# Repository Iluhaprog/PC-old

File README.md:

# Computer from scratch 

## Control unit

Операции
1. Сложение
2. Вычитание
3. Сдвиг влево
4. Сдвиг вправо
5. Записать значение в регистр A
6. Записать значение в регистр B
7. Условный переход при A > B
8. Условный переход при A < B
9. Условный переход при A = B
10. Завершить программу

> ### Условные обозначения
> 
> **RW**: read - "0", write - "1"
> 
> **EN**: enable - "1", disable - "0"
> 
> **HS**: hide - "1", show- "0"

> ### Устройства:
> - СК - Счетчик команд
> - РКК - Регистр кода команды
> - РА - Регистр А
> - РВ - Регистр В
> - РПА - Регистр пользовательского адреса
> - РР - Регистр результата
> - АЛУ - Арифметико-логичекое устройство
> - РФ - Регистр флагов

<h2>Формат команды</h2>
<div style="padding: 20px 10px 10px 20px; border-left: 2px solid grey; margin-bottom: 20px">

<span style="border: 3px solid orange">**код операции**</span>
<span style="border: 3px solid pink">адрес</span>

</div>

### 1. Операция сложения 

Код операции - **0001**

Адрес - номер места в ОЗУ, куда необходимо записать результат

Действия для выполнения:

1. Выключаем счетчик команд
2. Включаем чтение из ОЗУ **[R]** `0`
3. Включаем выводы ОЗУ **[EN]** `1` на чтение
4. Включаем запись в регистр пользовательских адресов (РПА) **[R]** `1`
5. Включаем выводы РПА **[EN]** для записи `1`
6. Выключаем выводы РПА **[EN]**  для записи `0`
7. Включаем запись в регистр кода команды (РКК) **[W]** `1`
8. Включаем выводы РКК **[EN]** для записи `1`
9. Выключаем выводы РКК **[EN]**  для записи `0`
10. Включаем чтение из РКК **[R]** `1`
11. Включаем выводы РКК **[EN]** для чтения `0`
12. Включаем выводы **Mode** `1`
13. Выключаем выводы ОЗУ **[EN]** `0` на чтение
14. Включаем выводы АЛУ **[EN]** для чтения
15. Включаем на запись регистр результата (РР) **[W]** `1`
16. Включаем выводы РР **[EN]** `1` для записи
17. Выключаем выводы РР **[EN]** `0` для записи
18. Выключаем выводы AЛУ **[EN]** `0` для чтения
19. Включаем чтение РР **[R]** `0`
20. Включаем выводы РР **[EN]** `1` для чтения
21. Выключаем вывод адреса из счетчика команд **[HS]** `1`
22. Включаем чтение РПА **[R]** `0`
23. Включаем выводы РПА **[EN]** `1` для чтения
24. Включаем ОЗУ на запись **[W]** `1`
25. Включаем выводы ОЗУ  **[EN]** `1` для записи
26. Выключаем выводы ОЗУ  **[EN]** `0` для записи
27. Выключаем выводы РПА **[EN]** `0` для чтения
28. Включаем вывод адреса из счетчика команд **[HS]** `0`
29. Выключаем выводы РР **[EN]** `0` для чтения
30. Включаем счетчик команд

Выводы :
1. EN СК
2. HS CK
3. EN ОЗУ
4. RW ОЗУ
5. EN РКК
6. RW РКК
7. EN PA
8. RW PA
9. EN PB
10. RW PB
11. EN PP
12. RW PP
13. EN РПА
14. RW РПА
15. АЛУ 1-бит (для выбора варианта работы АЛУ)
16. АЛУ 2-бит (для выбора варианта работы АЛУ)
17. EN АЛУ (чтение с выхода)
18. EN РФ
19. RW РФ

| Такт | Состояния на выходе   | Действия                   |
|------|-----------------------|----------------------------|
| 1    | 0010110000001100000   | 1,2,3,4,5,6,7,8            |
| 2    | 0000101010110000100   | 9,10,11,12,13,14,15,16     |
| 3    | 0111000000101000000   | 16,17,18,19,20,21,22,23,24 |
| 4    | 1000000000000000000   | 24,25,26,27,28,28,30       |

### 2. Операция вычитания 

Код операции - **0010**

Адрес - номер места в ОЗУ, куда необходимо записать результат

Действия для выполнения:

1. Выключаем счетчик команд
2. Включаем чтение из ОЗУ **[R]** `0`
3. Включаем выводы ОЗУ **[EN]** `1` на чтение
4. Включаем запись в регистр пользовательских адресов (РПА) **[R]** `1`
5. Включаем выводы РПА **[EN]** для записи `1`
6. Выключаем выводы РПА **[EN]**  для записи `0`
7. Включаем запись в регистр кода команды (РКК) **[W]** `1`
8. Включаем выводы РКК **[EN]** для записи `1`
9. Выключаем выводы РКК **[EN]**  для записи `0`
10. Включаем чтение из РКК **[R]** `1`
11. Включаем выводы РКК **[EN]** для чтения `0`
12. Включаем выводы **Mode** `10`
13. Выключаем выводы ОЗУ **[EN]** `0` на чтение
14. Включаем выводы АЛУ **[EN]** для чтения
15. Включаем на запись регистр результата (РР) **[W]** `1`
16. Включаем выводы РР **[EN]** `1` для записи
17. Выключаем выводы РР **[EN]** `0` для записи
18. Выключаем выводы AЛУ **[EN]** `0` для чтения
19. Включаем чтение РР **[R]** `0`
20. Включаем выводы РР **[EN]** `1` для чтения
21. Выключаем вывод адреса из счетчика команд **[HS]** `1`
22. Включаем чтение РПА **[R]** `0`
23. Включаем выводы РПА **[EN]** `1` для чтения
24. Включаем ОЗУ на запись **[W]** `1`
25. Включаем выводы ОЗУ  **[EN]** `1` для записи
26. Выключаем выводы ОЗУ  **[EN]** `0` для записи
27. Выключаем выводы РПА **[EN]** `0` для чтения
28. Включаем вывод адреса из счетчика команд **[HS]** `0`
29. Выключаем выводы РР **[EN]** `0` для чтения
30. Включаем счетчик команд

Выводы :
1. EN СК
2. HS CK
3. EN ОЗУ
4. RW ОЗУ
5. EN РКК
6. RW РКК
7. EN PA
8. RW PA
9. EN PB
10. RW PB
11. EN PP
12. RW PP
13. EN РПА
14. RW РПА
15. АЛУ 1-бит (для выбора варианта работы АЛУ)
16. АЛУ 2-бит (для выбора варианта работы АЛУ)
17. EN АЛУ (чтение с выхода)
18. EN РФ
19. RW РФ

| Такт | Состояния на выходе   | Действия                   |
|------|-----------------------|----------------------------|
| 1    | 0010110000001100000   | 1,2,3,4,5,6,7,8            |
| 2    | 0000101010110010100   | 9,10,11,12,13,14,15,16     |
| 3    | 0111000000101000000   | 16,17,18,19,20,21,22,23,24 |
| 4    | 1000000000000000000   | 24,25,26,27,28,28,30       |

### 3. Операция сдвига влево 

Код операции - **0011**

Адрес - номер места в ОЗУ, куда необходимо записать результат

Действия для выполнения:

1. Выключаем счетчик команд
2. Включаем чтение из ОЗУ **[R]** `0`
3. Включаем выводы ОЗУ **[EN]** `1` на чтение
4. Включаем запись в регистр пользовательских адресов (РПА) **[R]** `1`
5. Включаем выводы РПА **[EN]** для записи `1`
6. Выключаем выводы РПА **[EN]**  для записи `0`
7. Включаем запись в регистр кода команды (РКК) **[W]** `1`
8. Включаем выводы РКК **[EN]** для записи `1`
9. Выключаем выводы РКК **[EN]**  для записи `0`
10. Включаем чтение из РКК **[R]** `1`
11. Включаем выводы РКК **[EN]** для чтения `0`
12. Включаем выводы **Mode** `11`
13. Выключаем выводы ОЗУ **[EN]** `0` на чтение
14. Включаем выводы АЛУ **[EN]** для чтения
15. Включаем на запись регистр результата (РР) **[W]** `1`
16. Включаем выводы РР **[EN]** `1` для записи
17. Выключаем выводы РР **[EN]** `0` для записи
18. Выключаем выводы AЛУ **[EN]** `0` для чтения
19. Включаем чтение РР **[R]** `0`
20. Включаем выводы РР **[EN]** `1` для чтения
21. Выключаем вывод адреса из счетчика команд **[HS]** `1`
22. Включаем чтение РПА **[R]** `0`
23. Включаем выводы РПА **[EN]** `1` для чтения
24. Включаем ОЗУ на запись **[W]** `1`
25. Включаем выводы ОЗУ  **[EN]** `1` для записи
26. Выключаем выводы ОЗУ  **[EN]** `0` для записи
27. Выключаем выводы РПА **[EN]** `0` для чтения
28. Включаем вывод адреса из счетчика команд **[HS]** `0`
29. Выключаем выводы РР **[EN]** `0` для чтения
30. Включаем счетчик команд

Выводы :
1. EN СК
2. HS CK
3. EN ОЗУ
4. RW ОЗУ
5. EN РКК
6. RW РКК
7. EN PA
8. RW PA
9. EN PB
10. RW PB
11. EN PP
12. RW PP
13. EN РПА
14. RW РПА
15. АЛУ 1-бит (для выбора варианта работы АЛУ)
16. АЛУ 2-бит (для выбора варианта работы АЛУ)
17. EN АЛУ (чтение с выхода)
18. EN РФ
19. RW РФ

| Такт | Состояния на выходе   | Действия                   |
|------|-----------------------|----------------------------|
| 1    | 0010110000001100000   | 1,2,3,4,5,6,7,8            |
| 2    | 0000101010110011100   | 9,10,11,12,13,14,15,16     |
| 3    | 0111000000101000000   | 16,17,18,19,20,21,22,23,24 |
| 4    | 1000000000000000000   | 24,25,26,27,28,28,30       |

### 3. Операция сдвига вправо 

Код операции - **0100**

Адрес - номер места в ОЗУ, куда необходимо записать результат

Действия для выполнения:

1. Выключаем счетчик команд
2. Включаем чтение из ОЗУ **[R]** `0`
3. Включаем выводы ОЗУ **[EN]** `1` на чтение
4. Включаем запись в регистр пользовательских адресов (РПА) **[R]** `1`
5. Включаем выводы РПА **[EN]** для записи `1`
6. Выключаем выводы РПА **[EN]**  для записи `0`
7. Включаем запись в регистр кода команды (РКК) **[W]** `1`
8. Включаем выводы РКК **[EN]** для записи `1`
9. Выключаем выводы РКК **[EN]**  для записи `0`
10. Включаем чтение из РКК **[R]** `1`
11. Включаем выводы РКК **[EN]** для чтения `0`
12. Включаем выводы **Mode** `11`
13. Выключаем выводы ОЗУ **[EN]** `0` на чтение
14. Включаем выводы АЛУ **[EN]** для чтения
15. Включаем на запись регистр результата (РР) **[W]** `1`
16. Включаем выводы РР **[EN]** `1` для записи
17. Выключаем выводы РР **[EN]** `0` для записи
18. Выключаем выводы AЛУ **[EN]** `0` для чтения
19. Включаем чтение РР **[R]** `0`
20. Включаем выводы РР **[EN]** `1` для чтения
21. Выключаем вывод адреса из счетчика команд **[HS]** `1`
22. Включаем чтение РПА **[R]** `0`
23. Включаем выводы РПА **[EN]** `1` для чтения
24. Включаем ОЗУ на запись **[W]** `1`
25. Включаем выводы ОЗУ  **[EN]** `1` для записи
26. Выключаем выводы ОЗУ  **[EN]** `0` для записи
27. Выключаем выводы РПА **[EN]** `0` для чтения
28. Включаем вывод адреса из счетчика команд **[HS]** `0`
29. Выключаем выводы РР **[EN]** `0` для чтения
30. Включаем счетчик команд

Выводы :
1. EN СК
2. HS CK
3. EN ОЗУ
4. RW ОЗУ
5. EN РКК
6. RW РКК
7. EN PA
8. RW PA
9. EN PB
10. RW PB
11. EN PP
12. RW PP
13. EN РПА
14. RW РПА
15. АЛУ 1-бит (для выбора варианта работы АЛУ)
16. АЛУ 2-бит (для выбора варианта работы АЛУ)
17. EN АЛУ (чтение с выхода)
18. EN РФ
19. RW РФ

| Такт | Состояния на выходе   | Действия                   |
|------|-----------------------|----------------------------|
| 1    | 0010110000001100000   | 1,2,3,4,5,6,7,8            |
| 2    | 0000101010110001100   | 9,10,11,12,13,14,15,16     |
| 3    | 0111000000101000000   | 16,17,18,19,20,21,22,23,24 |
| 4    | 1000000000000000000   | 24,25,26,27,28,28,30       |

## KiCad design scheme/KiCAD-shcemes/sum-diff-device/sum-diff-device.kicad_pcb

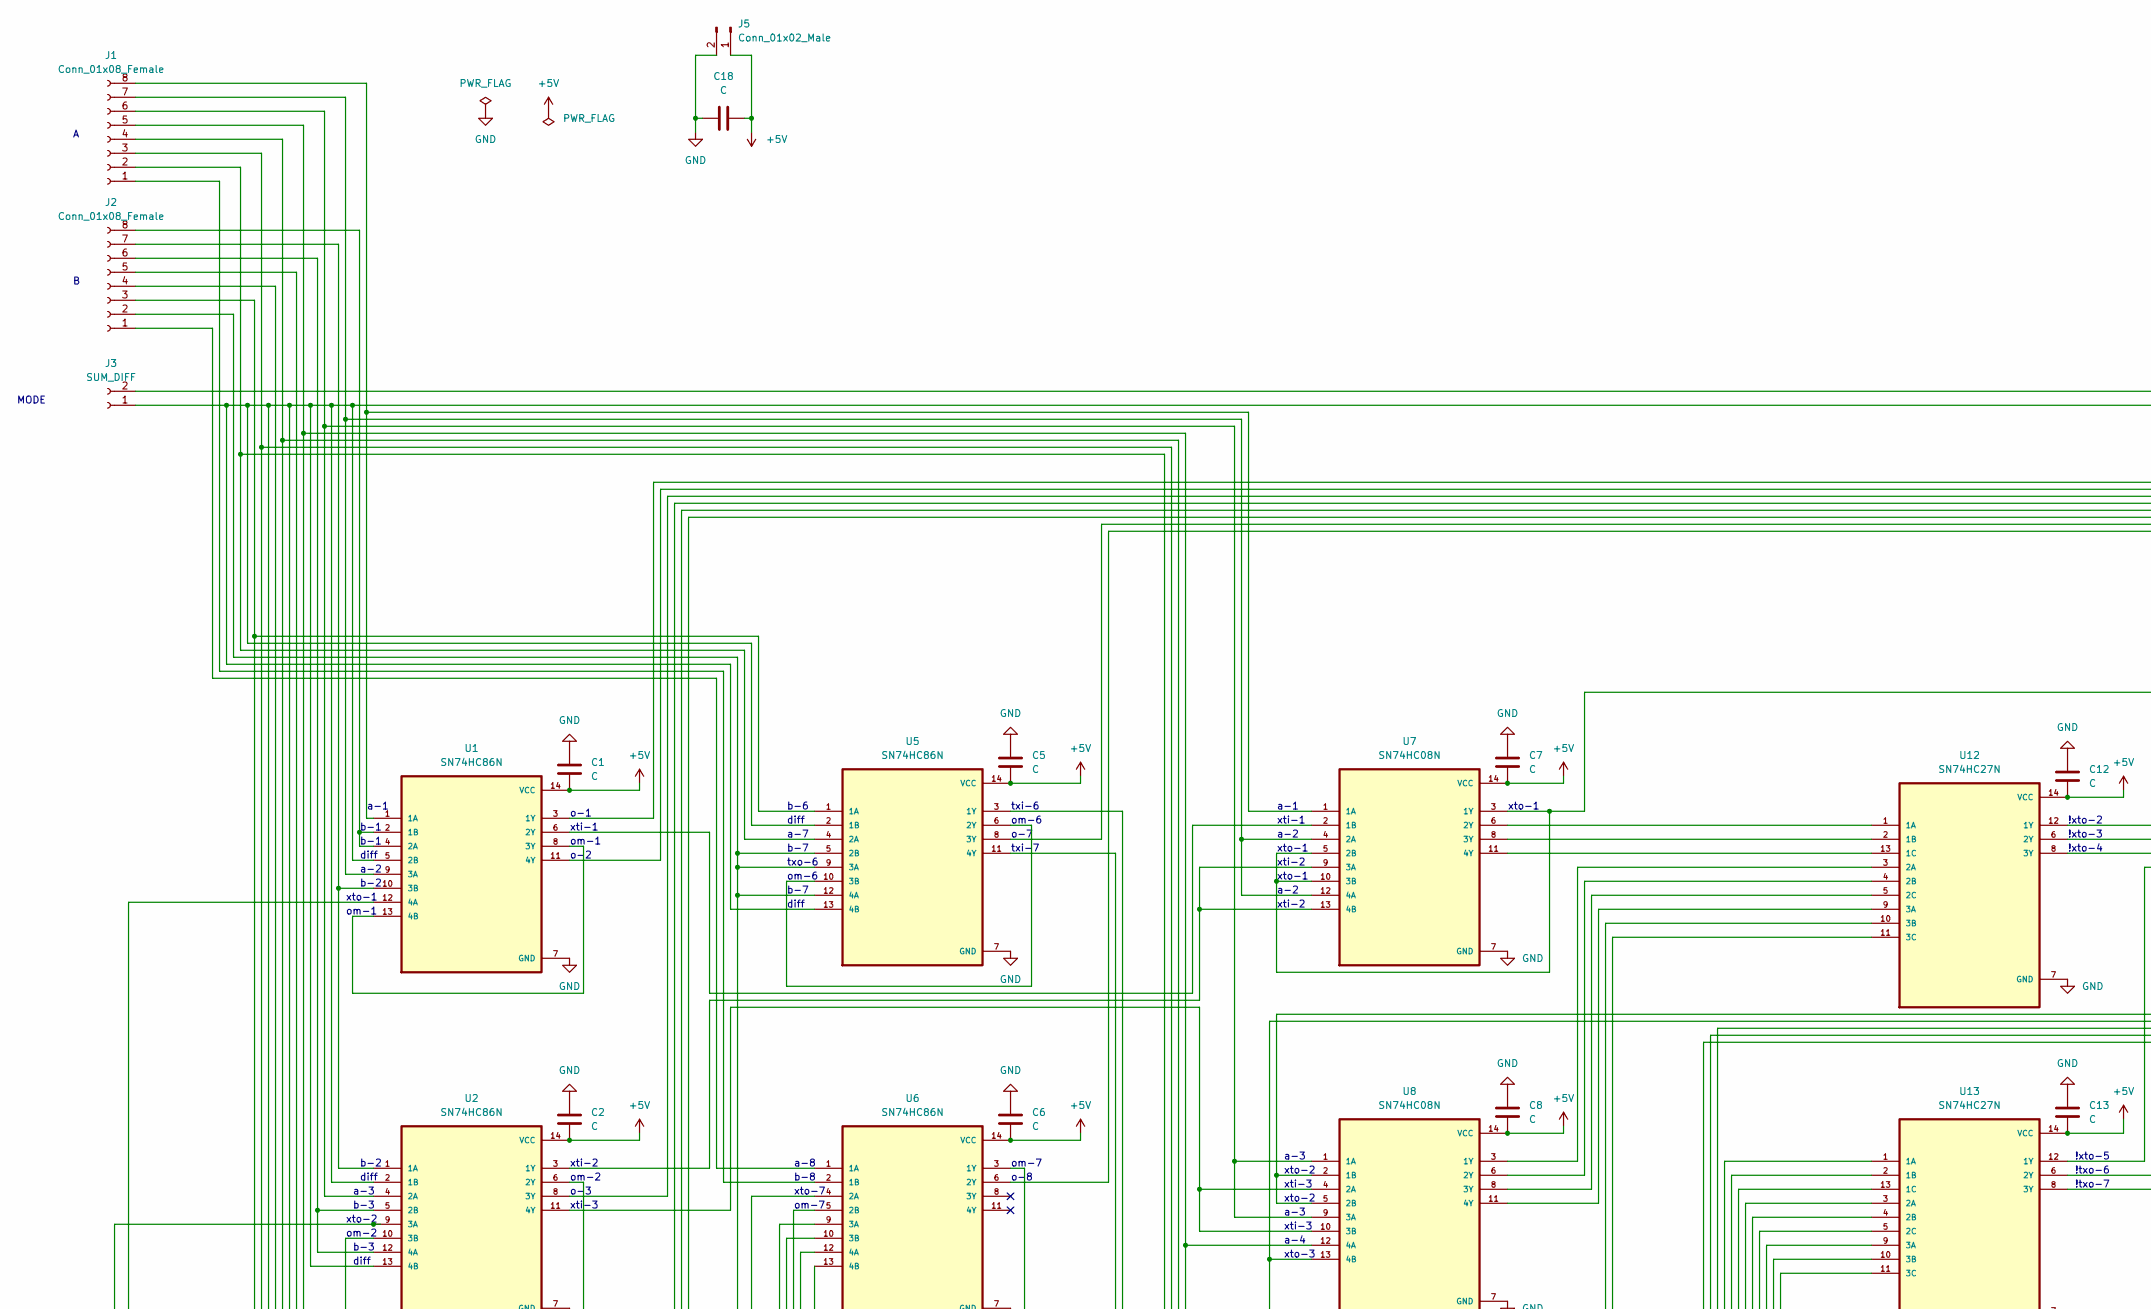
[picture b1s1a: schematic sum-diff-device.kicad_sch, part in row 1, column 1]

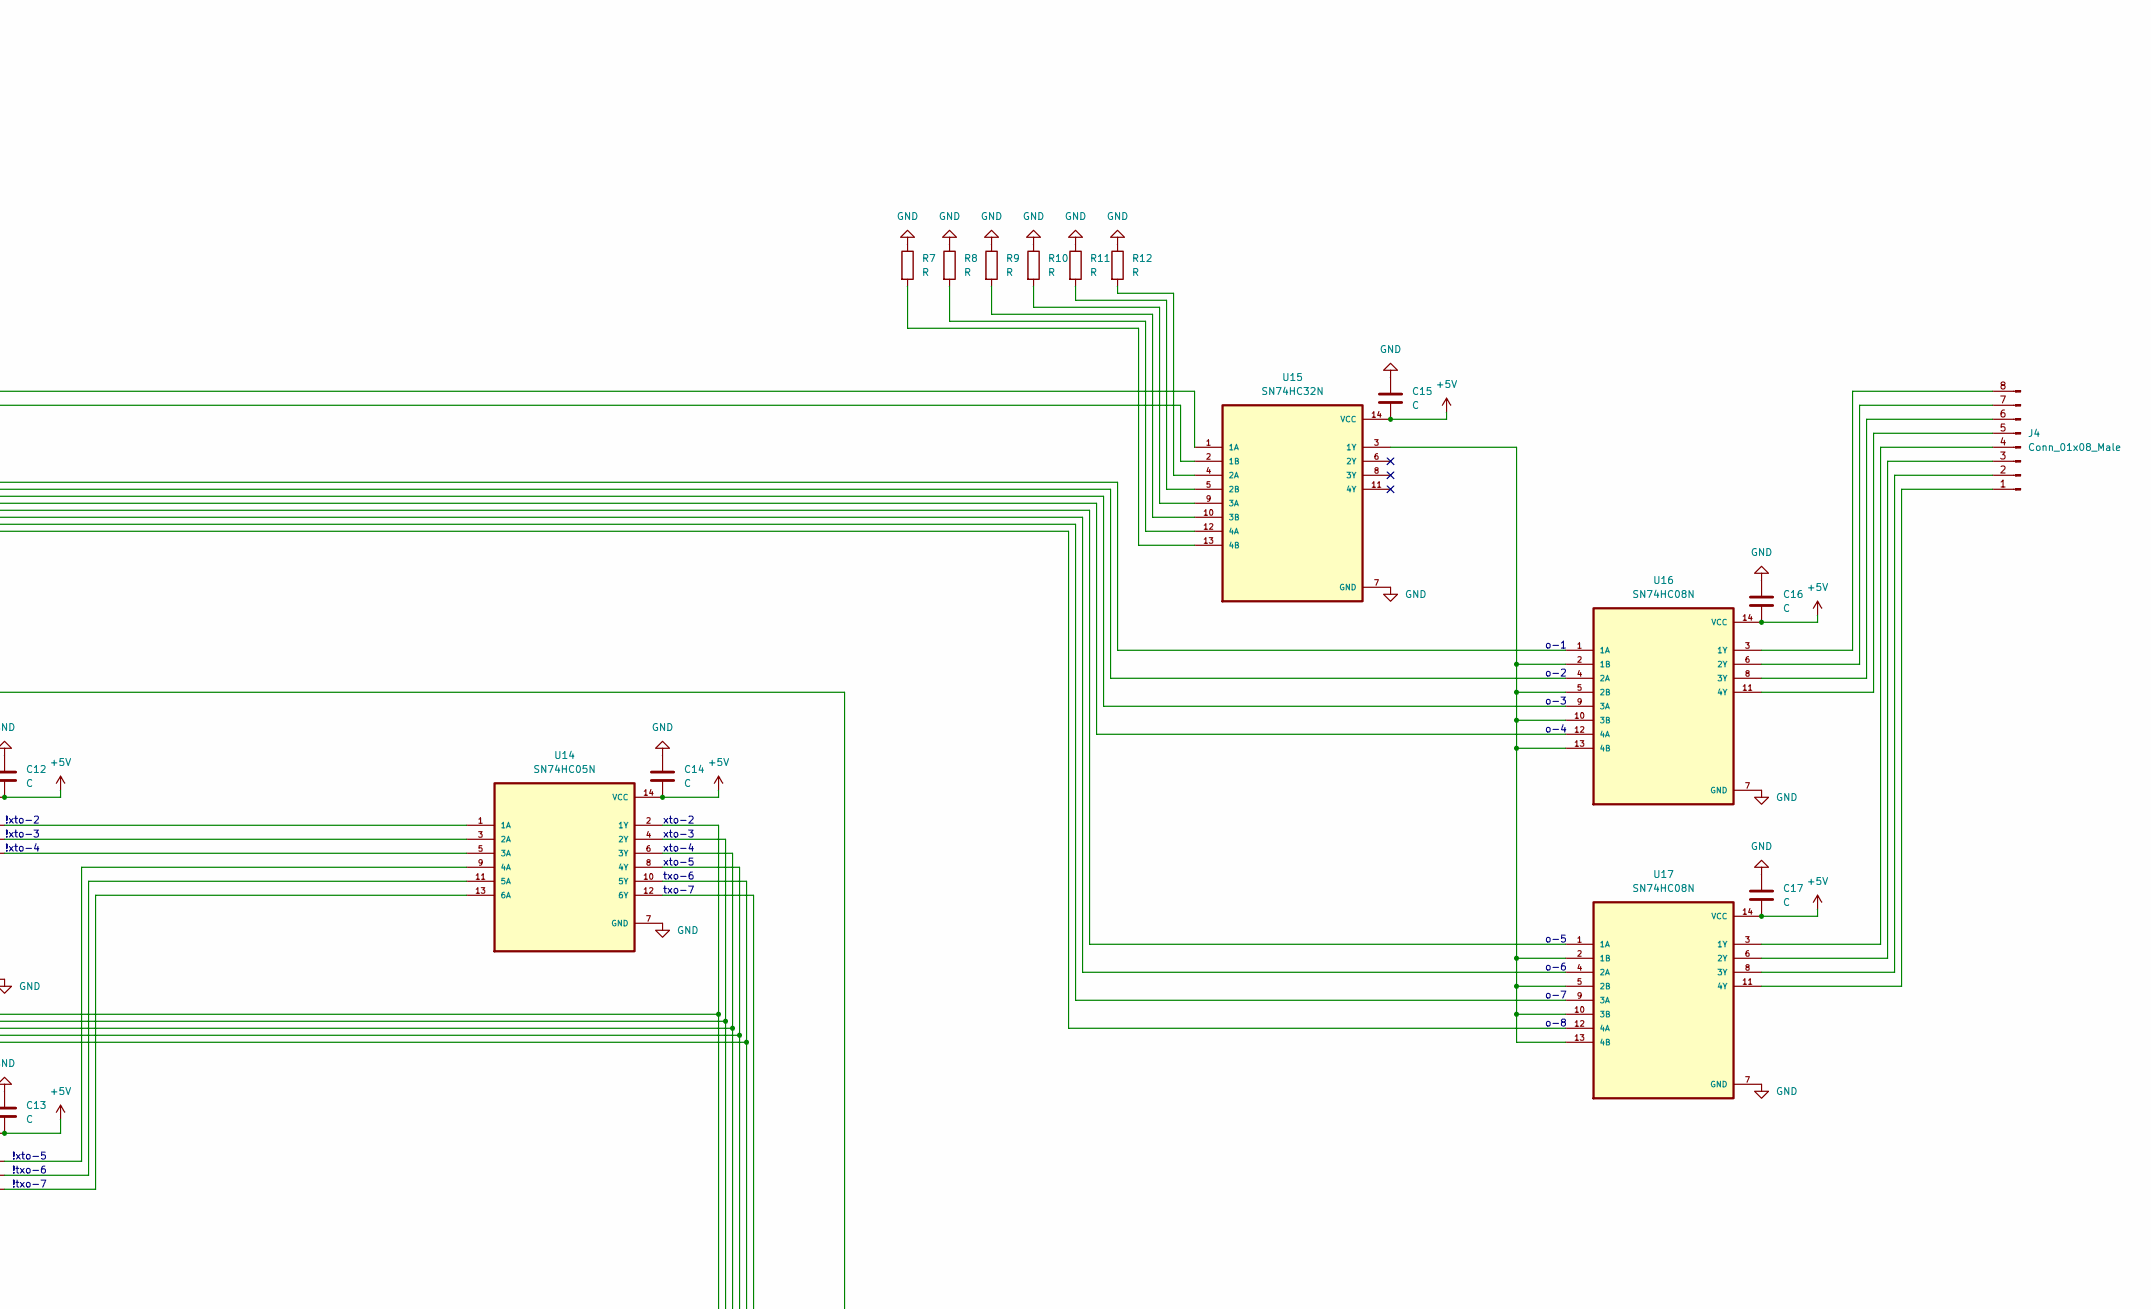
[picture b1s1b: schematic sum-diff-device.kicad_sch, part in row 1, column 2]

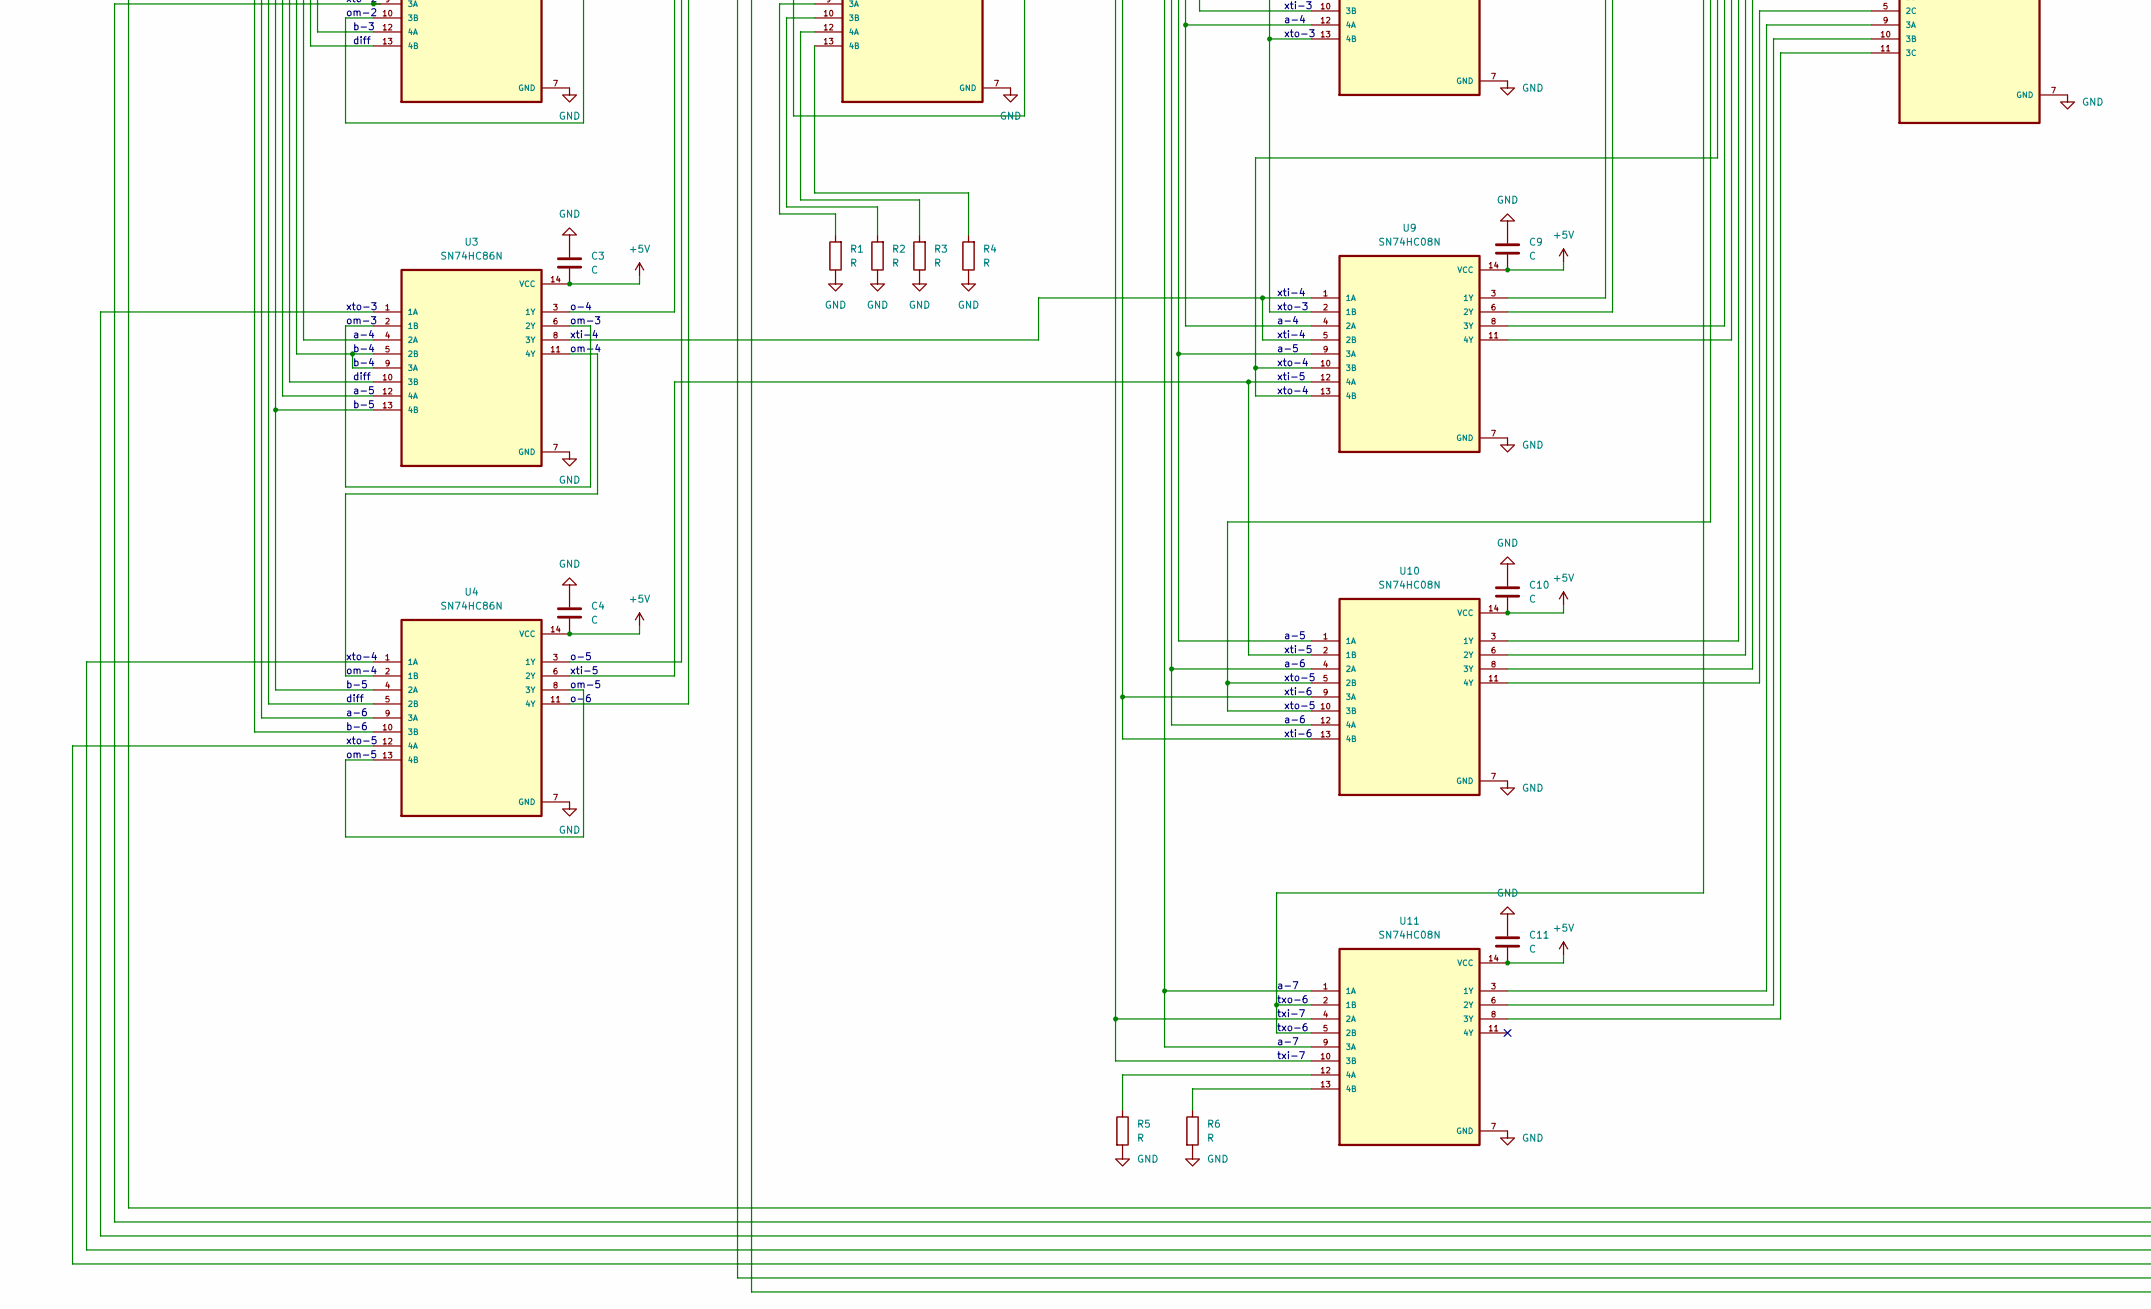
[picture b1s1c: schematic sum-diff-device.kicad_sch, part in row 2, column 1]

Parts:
C1, C2, C3, C4, C5, C6, C7, C8, C9, C10, C11, C12, C13, C14, C15, C16, C17: C; C_Rect_L7.0mm_W2.0mm_P5.00mm
C18: C; CP_Radial_D8.0mm_P5.00mm
J1, J2: Conn_01x08_Female; PinHeader_1x08_P2.54mm_Vertical
J3: SUM_DIFF; PinSocket_1x02_P2.54mm_Vertical
J4: Conn_01x08_Male; PinHeader_1x08_P2.54mm_Vertical
J5: Conn_01x02_Male; PinSocket_1x02_P2.54mm_Vertical
R1, R2, R3, R4, R5, R6, R7, R8, R9, R10, R11, R12: R; R_Axial_DIN0204_L3.6mm_D1.6mm_P5.08mm_Vertical
U1, U2, U3, U4, U5, U6: SN74HC86N; DIP794W45P254L1969H508Q14
U7, U8, U9, U10, U11, U16, U17: SN74HC08N; DIP794W45P254L1969H508Q14
U12, U13: SN74HC27N; DIP794W45P254L1969H508Q14
U14: SN74HC05N; DIP794W45P254L1969H508Q14
U15: SN74HC32N; DIP794W45P254L1969H508Q14

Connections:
+5V: C1.2, C2.2, C3.2, C4.2, C5.2, C6.2, C7.2, C8.2, C9.2, C10.2, C11.2, C12.2, C13.2, C14.2, C15.2, C16.2, C17.2, C18.2, J5.1, U1.14 (VCC), U2.14 (VCC), U3.14 (VCC), U4.14 (VCC), U5.14 (VCC), U6.14 (VCC), U7.14 (VCC), U8.14 (VCC), U9.14 (VCC), U10.14 (VCC), U11.14 (VCC), U12.14 (VCC), U13.14 (VCC), U14.14 (VCC), U15.14 (VCC), U16.14 (VCC), U17.14 (VCC)
GND: C1.1, C2.1, C3.1, C4.1, C5.1, C6.1, C7.1, C8.1, C9.1, C10.1, C11.1, C12.1, C13.1, C14.1, C15.1, C16.1, C17.1, C18.1, J5.2, R1.1, R2.1, R3.1, R4.1, R5.2, R6.2, R7.1, R8.1, R9.1, R10.1, R11.1, R12.1, U1.7 (GND), U2.7 (GND), U3.7 (GND), U4.7 (GND), U5.7 (GND), U6.7 (GND), U7.7 (GND), U8.7 (GND), U9.7 (GND), U10.7 (GND), U11.7 (GND), U12.7 (GND), U13.7 (GND), U14.7 (GND), U15.7 (GND), U16.7 (GND), U17.7 (GND)
unnamed: J1.1, U6.2 (1B)
unnamed: J1.2, U5.4 (2A), U11.1 (1A), U11.9 (3A)
unnamed: J1.4, U3.12 (4A), U9.9 (3A), U10.1 (1A)
unnamed: J1.5, U3.4 (2A), U8.12 (4A), U9.4 (2A)
unnamed: J1.6, U2.4 (2A), U8.1 (1A), U8.9 (3A)
unnamed: J1.7, U1.9 (3A), U7.4 (2A), U7.12 (4A)
unnamed: J1.8, U1.1 (1A), U7.1 (1A)
unnamed: J2.1, U6.1 (1A)
unnamed: J2.2, U5.5 (2B), U5.9 (3A), U5.12 (4A), U11.2 (1B), U11.5 (2B), U14.10 (5Y)
unnamed: J2.3, U4.10 (3B), U5.1 (1A)
unnamed: J2.4, U3.13 (4B), U4.4 (2A)
unnamed: J2.5, U3.5 (2B), U3.9 (3A)
unnamed: J2.7, U1.10 (3B), U2.1 (1A)
unnamed: J2.8, U1.2 (1B), U1.4 (2A)
unnamed: J3.1, U1.5 (2B), U2.2 (1B), U2.13 (4B), U3.10 (3B), U4.5 (2B), U5.2 (1B), U5.13 (4B), U15.2 (1B)
unnamed: J3.2, U15.1 (1A)
unnamed: J4.1, U17.11 (4Y)
unnamed: J4.2, U17.8 (3Y)
unnamed: J4.4, U17.3 (1Y)
unnamed: J4.5, U16.11 (4Y)
unnamed: J4.6, U16.8 (3Y)
unnamed: J4.8, U16.3 (1Y)
unnamed: R1.2, U6.9 (3A)
unnamed: R2.2, U6.10 (3B)
unnamed: R3.2, U6.12 (4A)
unnamed: R4.2, U6.13 (4B)
unnamed: R5.1, U11.12 (4A)
unnamed: R6.1, U11.13 (4B)
unnamed: R7.2, U15.13 (4B)
unnamed: R8.2, U15.12 (4A)
unnamed: R9.2, U15.10 (3B)
unnamed: R10.2, U15.9 (3A)
unnamed: R11.2, U15.5 (2B)
unnamed: R12.2, U15.4 (2A)
unnamed: U1.3 (1Y), U16.1 (1A)
unnamed: U1.6 (2Y), U7.2 (1B)
unnamed: U1.11 (4Y), U16.4 (2A)
unnamed: U1.12 (4A), U7.3 (1Y), U7.5 (2B), U7.10 (3B)
unnamed: U1.8 (3Y), U1.13 (4B)
unnamed: U2.3 (1Y), U7.9 (3A), U7.13 (4B)
unnamed: U2.6 (2Y), U2.10 (3B)
unnamed: U2.11 (4Y), U8.4 (2A), U8.10 (3B)
unnamed: J2.6, U2.5 (2B), U2.12 (4A)
unnamed: U3.2 (1B), U3.6 (2Y)
unnamed: U3.8 (3Y), U9.1 (1A), U9.5 (2B)
unnamed: U3.11 (4Y), U4.2 (1B)
unnamed: U4.8 (3Y), U4.13 (4B)
unnamed: U5.6 (2Y), U5.10 (3B)
unnamed: U6.3 (1Y), U6.5 (2B)
unnamed: U4.6 (2Y), U9.12 (4A), U10.2 (1B)
unnamed: U10.3 (1Y), U13.13 (1C)
unnamed: U10.6 (2Y), U13.3 (2A)
unnamed: U10.8 (3Y), U13.4 (2B)
unnamed: U4.12 (4A), U10.5 (2B), U10.10 (3B), U14.8 (4Y)
unnamed: U10.11 (4Y), U13.5 (2C)
unnamed: J1.3, U4.9 (3A), U10.4 (2A), U10.12 (4A)
unnamed: U5.3 (1Y), U10.9 (3A), U10.13 (4B)
unnamed: U11.3 (1Y), U13.9 (3A)
unnamed: U11.6 (2Y), U13.10 (3B)
unnamed: U11.8 (3Y), U13.11 (3C)
unnamed: U5.11 (4Y), U11.4 (2A), U11.10 (3B)
unnamed: U7.6 (2Y), U12.1 (1A)
unnamed: U7.8 (3Y), U12.2 (1B)
unnamed: U8.3 (1Y), U12.3 (2A)
unnamed: U8.6 (2Y), U12.4 (2B)
unnamed: U8.8 (3Y), U12.5 (2C)
unnamed: U12.6 (2Y), U14.3 (2A)
unnamed: U12.8 (3Y), U14.5 (3A)
unnamed: U8.11 (4Y), U12.9 (3A)
unnamed: U9.3 (1Y), U12.10 (3B)
unnamed: U9.6 (2Y), U12.11 (3C)
unnamed: U12.12 (1Y), U14.1 (1A)
unnamed: U7.11 (4Y), U12.13 (1C)
unnamed: U9.8 (3Y), U13.1 (1A)
unnamed: U9.11 (4Y), U13.2 (1B)
unnamed: U13.6 (2Y), U14.11 (5A)
unnamed: U13.8 (3Y), U14.13 (6A)
unnamed: U13.12 (1Y), U14.9 (4A)
unnamed: U2.9 (3A), U8.2 (1B), U8.5 (2B), U14.2 (1Y)
unnamed: U3.1 (1A), U8.13 (4B), U9.2 (1B), U14.4 (2Y)
unnamed: U4.1 (1A), U9.10 (3B), U9.13 (4B), U14.6 (3Y)
unnamed: U6.4 (2A), U14.12 (6Y)
unnamed: U15.3 (1Y), U16.2 (1B), U16.5 (2B), U16.10 (3B), U16.13 (4B), U17.2 (1B), U17.5 (2B), U17.10 (3B), U17.13 (4B)
unnamed: J4.7, U16.6 (2Y)
unnamed: U2.8 (3Y), U16.9 (3A)
unnamed: U3.3 (1Y), U16.12 (4A)
unnamed: U4.3 (1Y), U17.1 (1A)
unnamed: U4.11 (4Y), U17.4 (2A)
unnamed: J4.3, U17.6 (2Y)
unnamed: U5.8 (3Y), U17.9 (3A)
unnamed: U6.6 (2Y), U17.12 (4A)

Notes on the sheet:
a-5
xto-3
MODE
b-4
txi-7
a-3
b-2
b-3
om-2
om-7
a-6
o-1
xto-1
b-6
xti-5
om-6
diff
xti-2
!xto-5
xti-4
o-5
b-5
a-4
a-2
om-5
o-2
xto-5
o-7
xto-2
a-7
a-1
o-8
xti-3
om-3
om-4
o-4
a-8
xti-6
txo-6
b-1

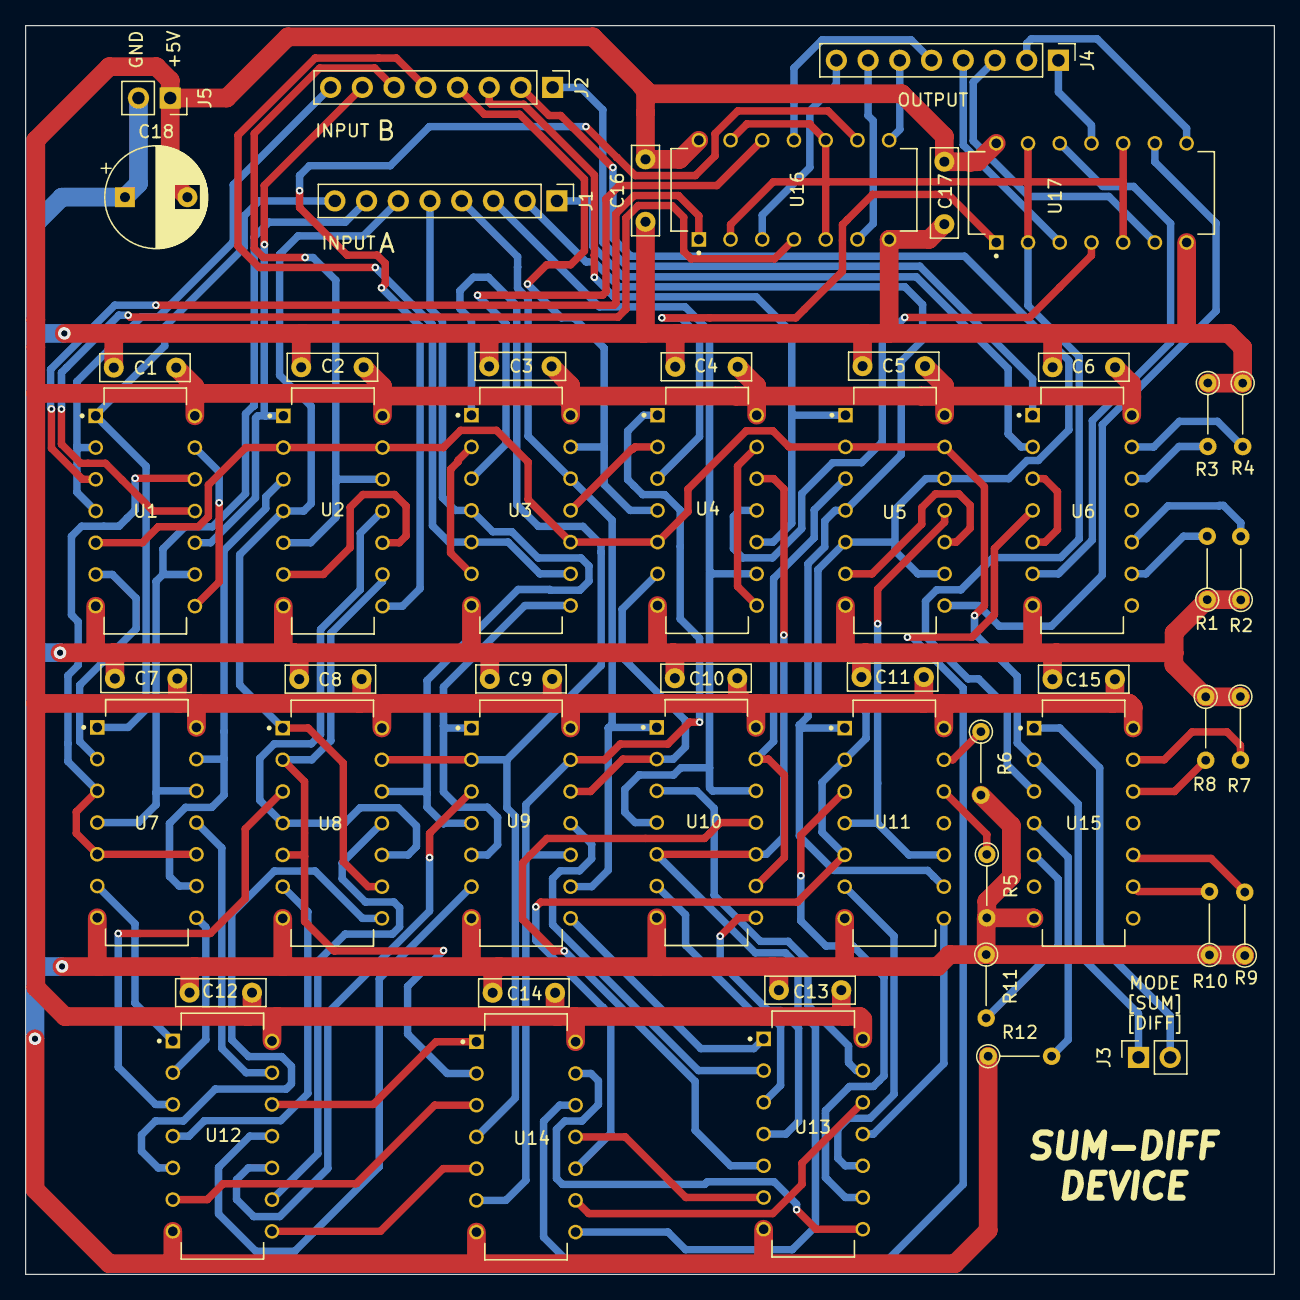
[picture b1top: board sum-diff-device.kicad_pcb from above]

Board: 2 copper layers, 100.0 x 100.0 mm, 52 parts (0 on the bottom side), 93 nets.

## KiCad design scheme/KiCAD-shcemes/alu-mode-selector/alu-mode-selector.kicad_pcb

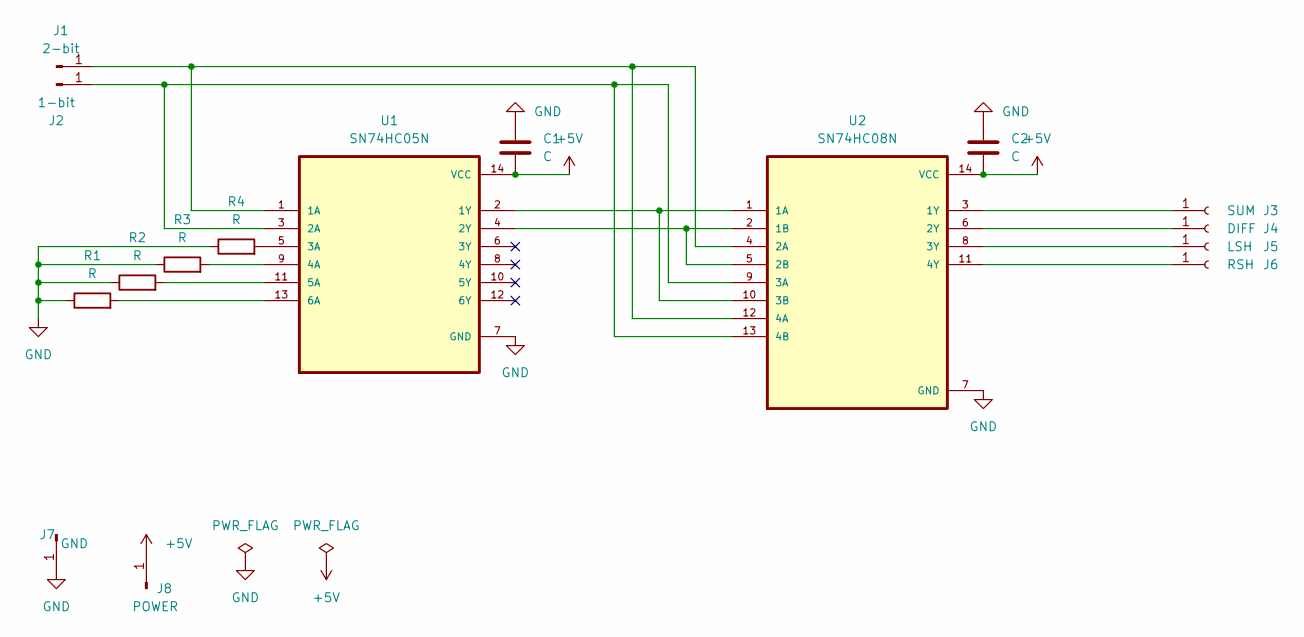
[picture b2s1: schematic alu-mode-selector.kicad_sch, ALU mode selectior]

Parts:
C1, C2: C; C_Rect_L7.0mm_W2.0mm_P5.00mm
J1: 2-bit; Pin_D1.3mm_L11.3mm_W2.8mm_Flat
J2: 1-bit; Pin_D1.3mm_L11.3mm_W2.8mm_Flat
J3: SUM; Pin_D1.3mm_L11.3mm_W2.8mm_Flat
J4: DIFF; Pin_D1.3mm_L11.3mm_W2.8mm_Flat
J5: LSH; Pin_D1.3mm_L11.3mm_W2.8mm_Flat
J6: RSH; Pin_D1.3mm_L11.3mm_W2.8mm_Flat
J7: GND; Pin_D1.3mm_L11.3mm_W2.8mm_Flat
J8: POWER; Pin_D1.3mm_L11.3mm_W2.8mm_Flat
R1, R2, R3, R4: R; R_Axial_DIN0411_L9.9mm_D3.6mm_P5.08mm_Vertical
U1: SN74HC05N; DIP794W45P254L1969H508Q14
U2: SN74HC08N; DIP794W45P254L1969H508Q14

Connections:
+5V: C1.1, C2.1, J8.1, U1.14 (VCC), U2.14 (VCC)
GND: C1.2, C2.2, J7.1, R1.1, R2.1, R3.1, R4.1, U1.7 (GND), U2.7 (GND)
unnamed: J1.1, U1.1 (1A), U2.4 (2A), U2.12 (4A)
unnamed: J2.1, U1.3 (2A), U2.9 (3A), U2.13 (4B)
unnamed: J3.1, U2.3 (1Y)
unnamed: J4.1, U2.6 (2Y)
unnamed: J5.1, U2.8 (3Y)
unnamed: J6.1, U2.11 (4Y)
unnamed: R1.2, U1.13 (6A)
unnamed: R2.2, U1.11 (5A)
unnamed: R3.2, U1.9 (4A)
unnamed: R4.2, U1.5 (3A)
unnamed: U1.2 (1Y), U2.1 (1A), U2.10 (3B)
unnamed: U1.4 (2Y), U2.2 (1B), U2.5 (2B)

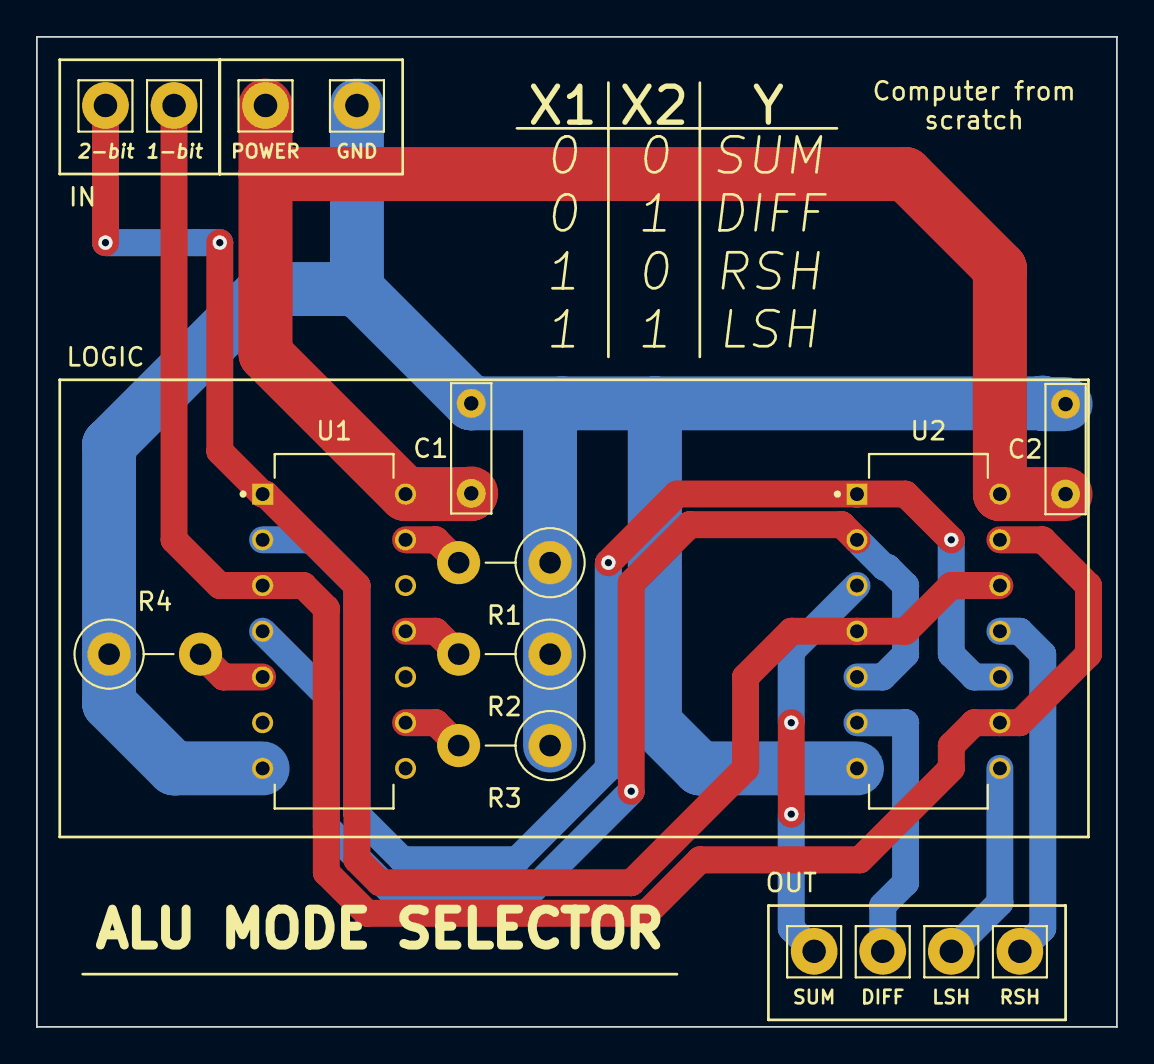
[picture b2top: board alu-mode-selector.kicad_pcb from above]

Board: 2 copper layers, 60.0 x 55.0 mm, 16 parts (0 on the bottom side), 14 nets.

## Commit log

2022-09-23 feat: Created circuit for ALU.
2022-09-23 feat: Added readme file.
2022-09-23 refactor: Changed name for readme.
2022-10-28 feat: Added common arch of computer, added description for sum operation, added template for CU IN/OUT
2022-11-02 Added sum, subtraction, shift left, shift right to CU. Added descriptions for these commands.
2022-12-05 feat: Added pcb for ALU.
2022-12-06 feat: Complete pcb for SUM/DIFF device.
2023-01-07 feat: last version of pcb
2023-01-25 feat: Changed pcb for sum-diff device
2023-02-02 last changes
2023-02-04 feat: Created build for jlcpcb.
2023-02-05 feat: Added gitignore.
2023-02-05 feat: Added basic devices for emulator.
2023-02-16 feat: Added instructions set.
2023-02-16 feat: Added Enum with commands.
2023-02-17 feat: Changed spec
